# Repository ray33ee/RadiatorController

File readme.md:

# RadiatorController

A home made WiFi operated radiator valve controller made using a Danfoss Eco enclosure and motor.

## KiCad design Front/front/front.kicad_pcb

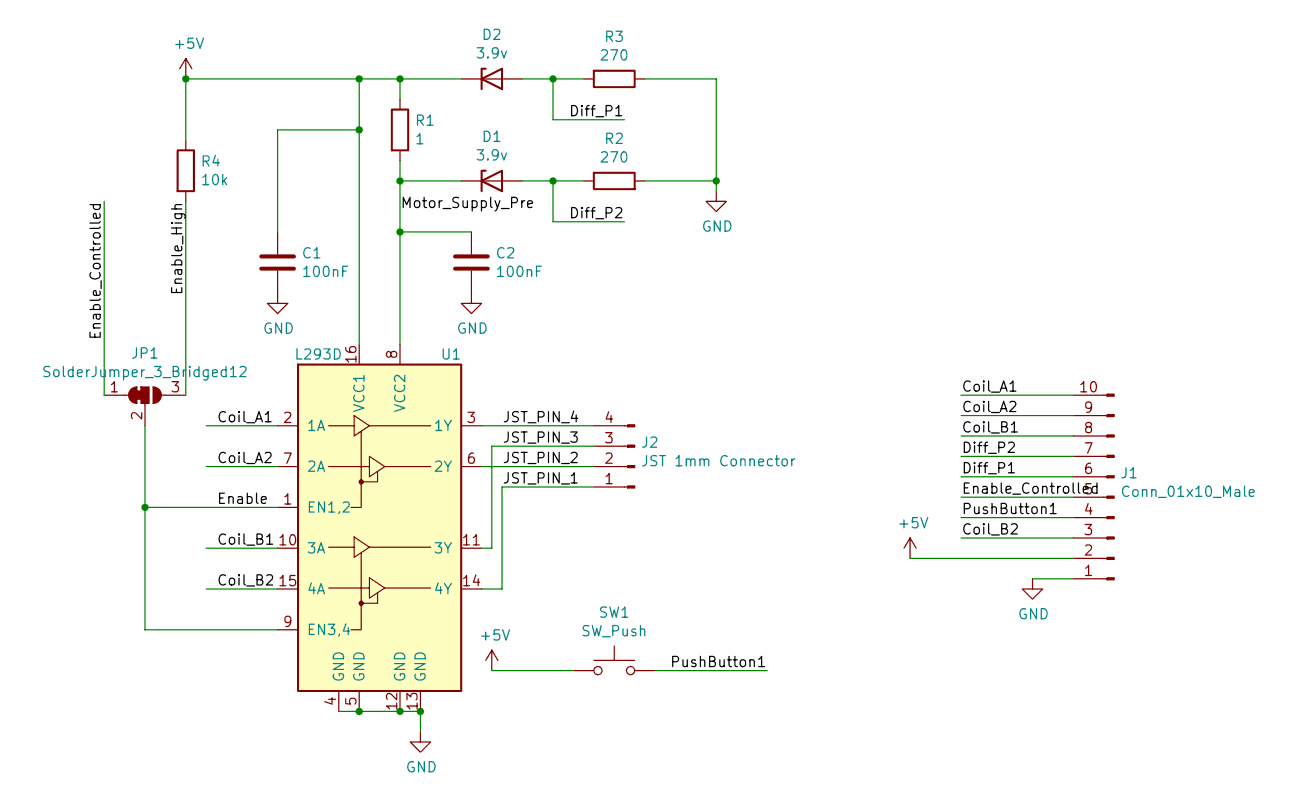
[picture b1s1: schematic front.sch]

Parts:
C1, C2: 100nF; C_1206_3216Metric_Pad1.33x1.80mm_HandSolder
D1, D2: 3.9v; D_MiniMELF
J1: Conn_01x10_Male; PinHeader_1x10_P2.54mm_Vertical
J2: JST 1mm Connector; JST_SH_SM04B-SRSS-TB_1x04-1MP_P1.00mm_Horizontal
JP1: SolderJumper_3_Bridged12; SolderJumper-3_P1.3mm_Bridged12_RoundedPad1.0x1.5mm_NumberL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
R1: 1; R_1206_3216Metric_Pad1.30x1.75mm_HandSolder
R2, R3: 270; R_1206_3216Metric_Pad1.30x1.75mm_HandSolder
R4: 10k; R_1206_3216Metric_Pad1.30x1.75mm_HandSolder
SW1: SW_Push; SW_Push_SPST_NO_Alps_SKRK
U1: L293D; DIP-16_W7.62mm

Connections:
+5V: C1.1, D2.1 (K), J1.2, R1.1, R4.1, SW1.1, U1.16 (VCC1)
/Coil_A1: J1.10, U1.2 (1A)
/Coil_A2: J1.9, U1.7 (2A)
/Coil_B1: J1.8, U1.10 (3A)
/Coil_B2: J1.3, U1.15 (4A)
/Diff_P1: D2.2 (A), J1.6, R3.2
/Diff_P2: D1.2 (A), J1.7, R2.1
/Enable: JP1.2 (C), U1.1 (EN1,2), U1.9 (EN3,4)
/Enable_Controlled: J1.5, JP1.1 (A)
/Enable_High: JP1.3 (B), R4.2
/JST_PIN_1: J2.1, U1.14 (4Y)
/JST_PIN_2: J2.2, U1.6 (2Y)
/JST_PIN_3: J2.3, U1.11 (3Y)
/JST_PIN_4: J2.4, U1.3 (1Y)
/Motor_Supply_Pre: C2.1, D1.1 (K), R1.2, U1.8 (VCC2)
/PushButton1: J1.4, SW1.2
GND: C1.2, C2.2, J1.1, R2.2, R3.1, U1.4 (GND), U1.5 (GND), U1.12 (GND), U1.13 (GND)

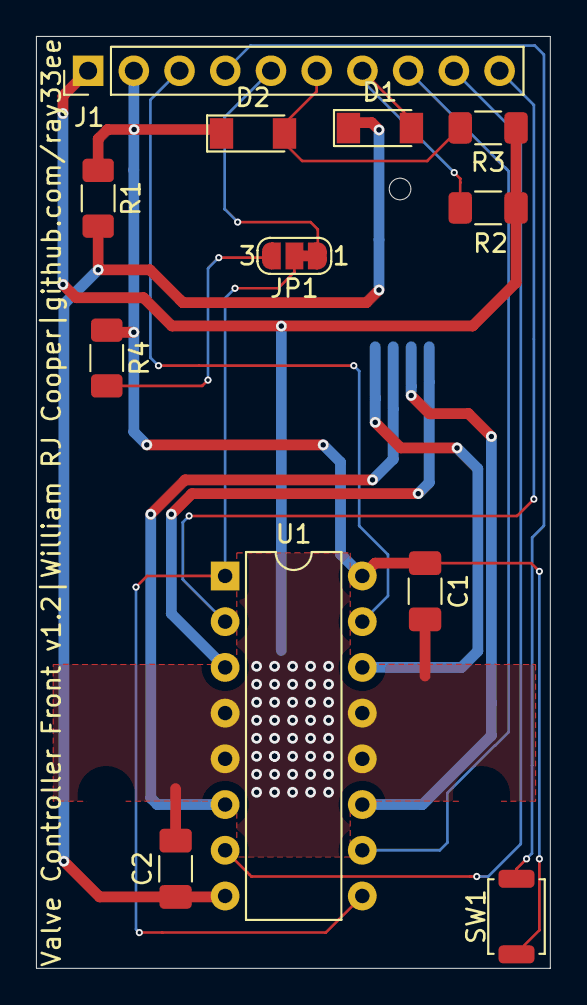
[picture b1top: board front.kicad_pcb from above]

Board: 2 copper layers, 28.5 x 51.8 mm, 13 parts (1 on the bottom side), 17 nets.

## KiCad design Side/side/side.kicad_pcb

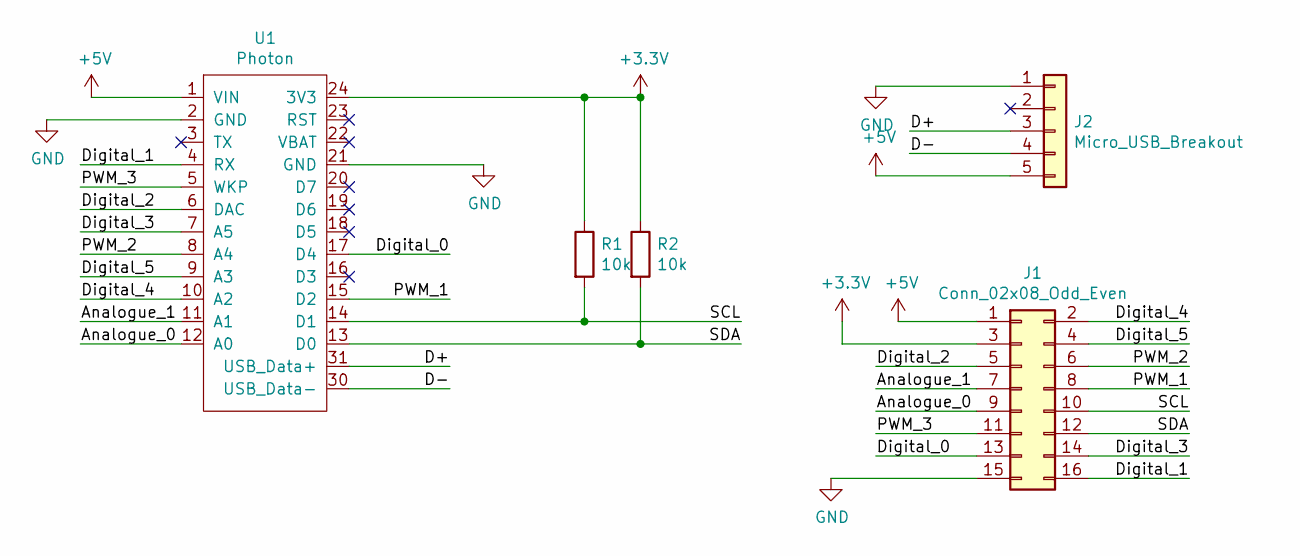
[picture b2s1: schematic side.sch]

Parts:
J1: Conn_02x08_Odd_Even; PinHeader_2x08_P2.54mm_Vertical
J2: Micro_USB_Breakout; Adafruit_Micro_USB_Breakout_copy
R1, R2: 10k; R_1206_3216Metric_Pad1.30x1.75mm_HandSolder
U1: Photon

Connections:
+3V3: J1.3, R1.1, R2.1, U1.24 (3V3)
+5V: J1.1, J2.5, U1.1 (VIN)
/Analogue_0: J1.9, U1.12 (A0)
/Analogue_1: J1.7, U1.11 (A1)
/D+: J2.3, U1.31 (USB_Data+)
/D-: J2.4, U1.30 (USB_Data-)
/Digital_0: J1.13, U1.17 (D4)
/Digital_1: J1.16, U1.4 (RX)
/Digital_2: J1.5, U1.6 (DAC)
/Digital_3: J1.14, U1.7 (A5)
/Digital_4: J1.2, U1.10 (A2)
/Digital_5: J1.4, U1.9 (A3)
/PWM_1: J1.8, U1.15 (D2)
/PWM_2: J1.6, U1.8 (A4)
/PWM_3: J1.11, U1.5 (WKP)
/SCL: J1.10, R1.2, U1.14 (D1)
/SDA: J1.12, R2.2, U1.13 (D0)
GND: J1.15, J2.1, U1.2 (GND), U1.21 (GND)

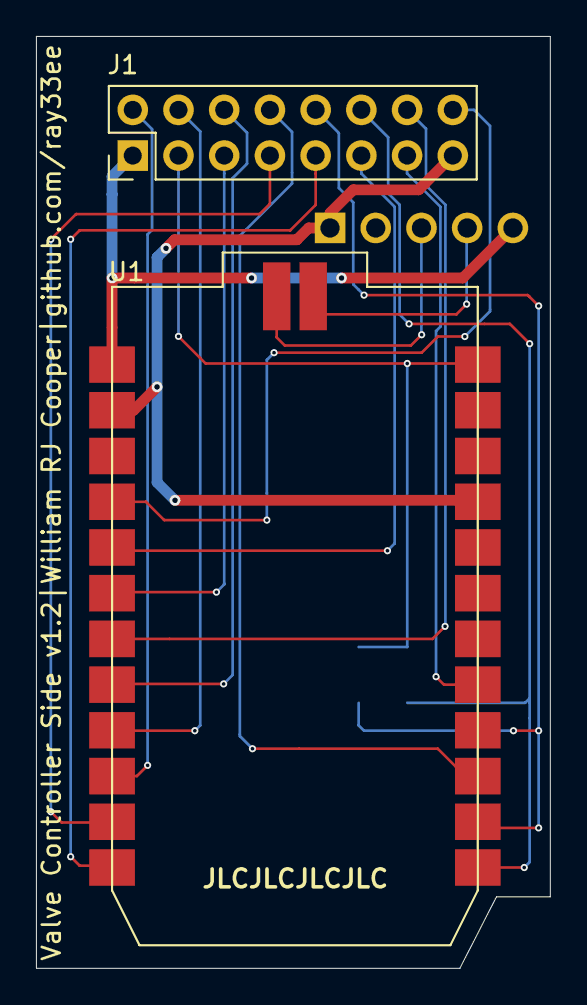
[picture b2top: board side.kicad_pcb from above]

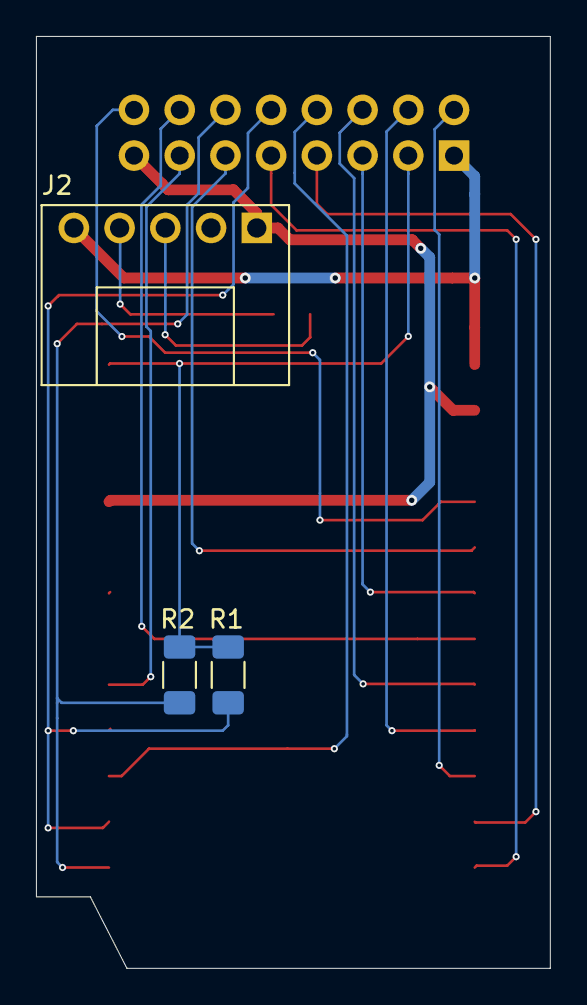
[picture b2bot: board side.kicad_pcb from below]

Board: 2 copper layers, 28.5 x 51.8 mm, 5 parts (3 on the bottom side), 18 nets.

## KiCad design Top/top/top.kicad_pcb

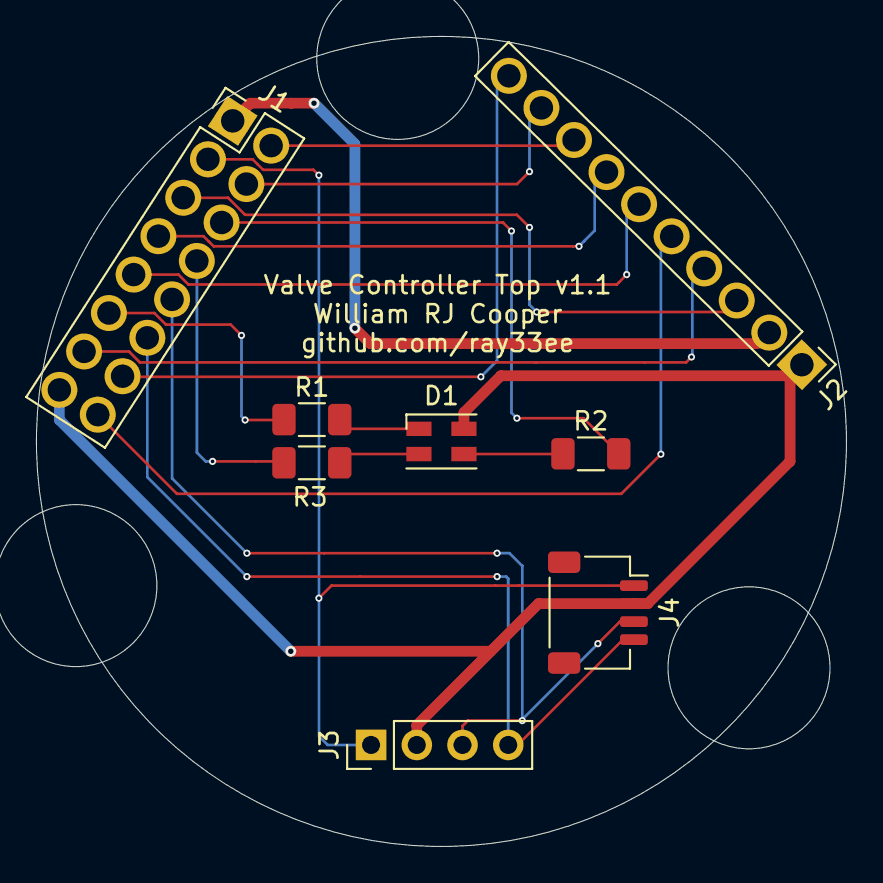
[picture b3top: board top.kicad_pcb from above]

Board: 2 copper layers, 45.0 x 45.0 mm, 11 parts (0 on the bottom side), 19 nets.

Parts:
D1: LED_RBGA; LED_Cree-PLCC4_3.2x2.88mm_CCW_Hand_Solder
J1: Conn_02x08_Odd_Even; PinHeader_2x08_P2.54mm_Vertical
J2: Conn_01x10_Female; PinHeader_1x10_P2.54mm_Vertical
J3: Header; PinHeader_1x04_P2.54mm_Vertical
J4: JST Connector; JST_SH_SM04B-SRSS-TB_1x04-1MP_P1.00mm_Horizontal
MH1, MH2, MH3: GenericMountingHole
R1: 680; R_1206_3216Metric_Pad1.30x1.75mm_HandSolder
R2, R3: 470; R_1206_3216Metric_Pad1.30x1.75mm_HandSolder

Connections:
+3V3: J1.3, J3.1, J4.1
+5V: J1.1, J2.2
/B: D1.2, R3.1
/Coil_A1: J1.14, J2.10
/Coil_A2: J1.4, J2.9
/Coil_B1: J1.2, J2.8
/Coil_B2: J1.5, J2.3
/Diff_P1: J1.9, J2.6
/Diff_P2: J1.7, J2.7
/Enabled_Controlled: J1.16, J2.5
/G: D1.3, R2.1
/LED_Blue: J1.8, R3.2
/LED_Green: J1.6, R2.2
/LED_Red: J1.11, R1.2
/PushButton: J1.13, J2.4
/R: D1.1, R1.1
/SCL: J1.10, J3.3, J4.3
/SDA: J1.12, J3.4, J4.4
GND: D1.4, J1.15, J2.1, J3.2, J4.2

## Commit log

2021-10-16 Version 0.1.0 - Initial commit
2021-10-16 Version 0.1.1 - Various changes, see changelog
2021-10-17 Version 0.1.2 - First draft of front PCB complete
2021-10-18 Version 0.1.3 - Various changes, see changelog
2021-10-19 Version 0.1.4 - Various changes, see changelog
2021-10-19 Version 0.1.5 - Various changes, see changelog
2021-10-20 Version 0.1.6 - Various changes, see changelog
2021-10-21 Version 0.1.7 - Various changes, see changelog
2021-10-23 Version 0.1.8 - Various changes, see changelog
2021-10-25 Version 0.1.9 - Various changes, see changelog
2021-10-26 Version 0.1.10 - Various changes, see changelog
2021-10-27 Version 0.1.11 - Various changes, see changelog
2021-10-29 Version 0.1.12 - Various changes, see changelog
2021-10-30 Version 0.1.13 - Various changes, see changelog
2021-10-31 Version 0.1.14 - Various changes, see changelog
2021-11-02 Version 0.1.15 - Various changes, see changelog
2021-11-04 Version 0.1.16 - Various changes, see changelog
2021-11-17 Version 0.1.17 - Modified code to accomodate Front/Side/Board PCBs
2021-11-19 Version 0.1.18 - Various changes, see changelog
2021-11-20 Version 0.1.19 - Various changes, see changelog
